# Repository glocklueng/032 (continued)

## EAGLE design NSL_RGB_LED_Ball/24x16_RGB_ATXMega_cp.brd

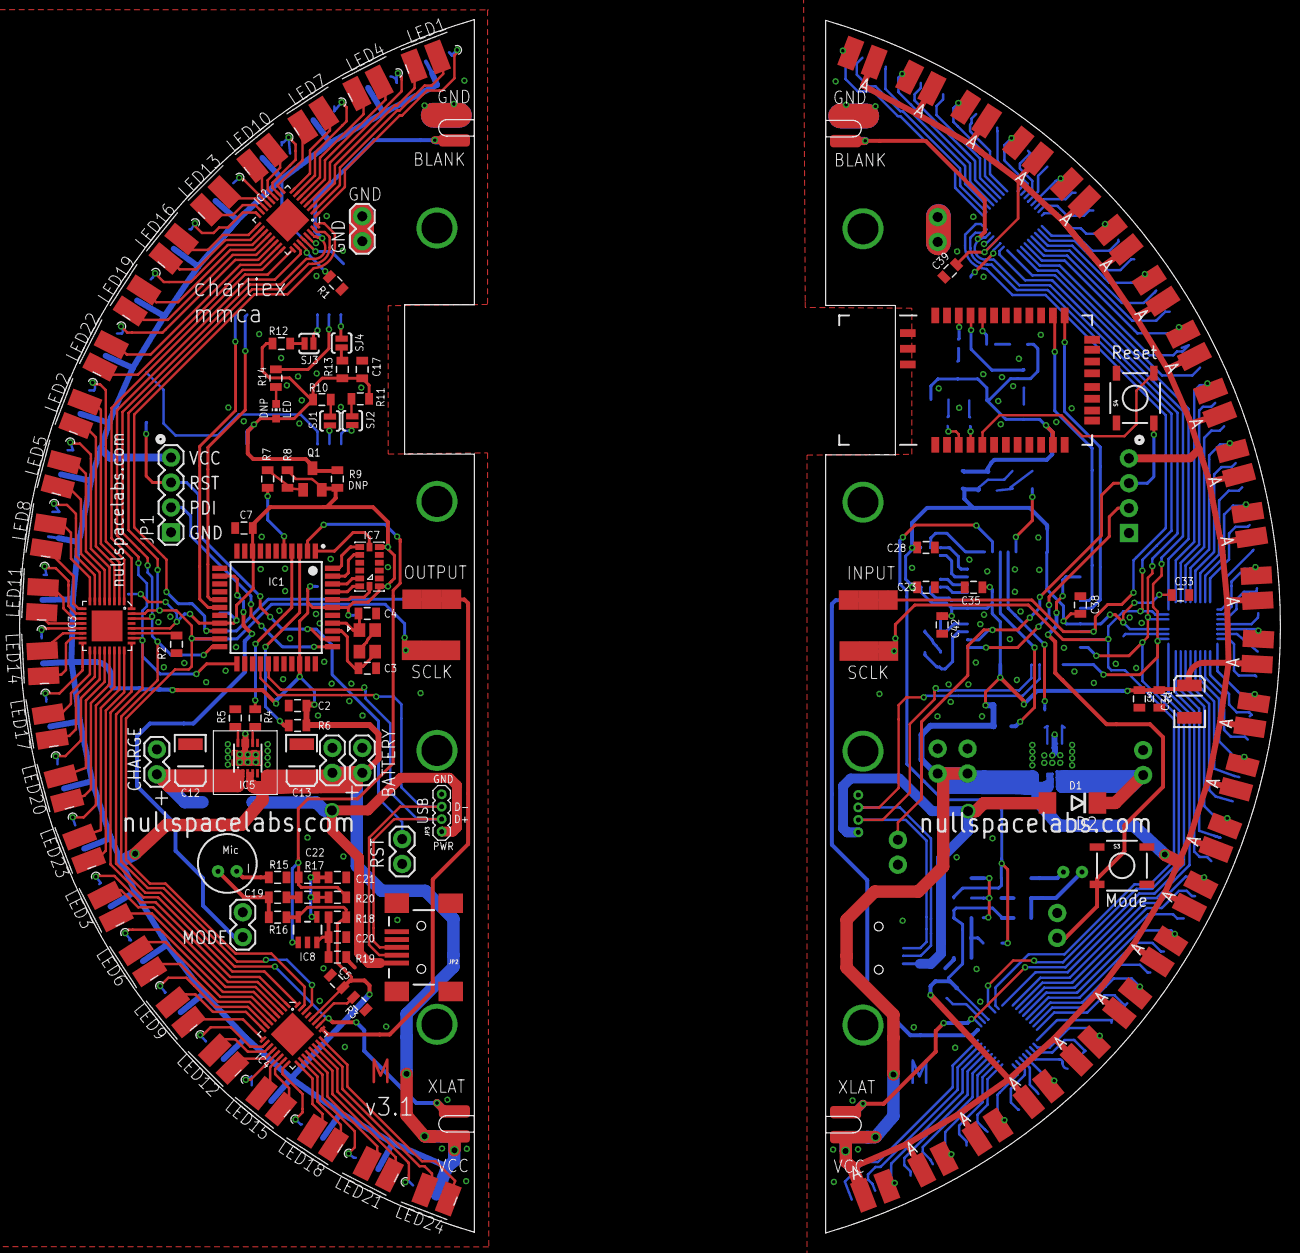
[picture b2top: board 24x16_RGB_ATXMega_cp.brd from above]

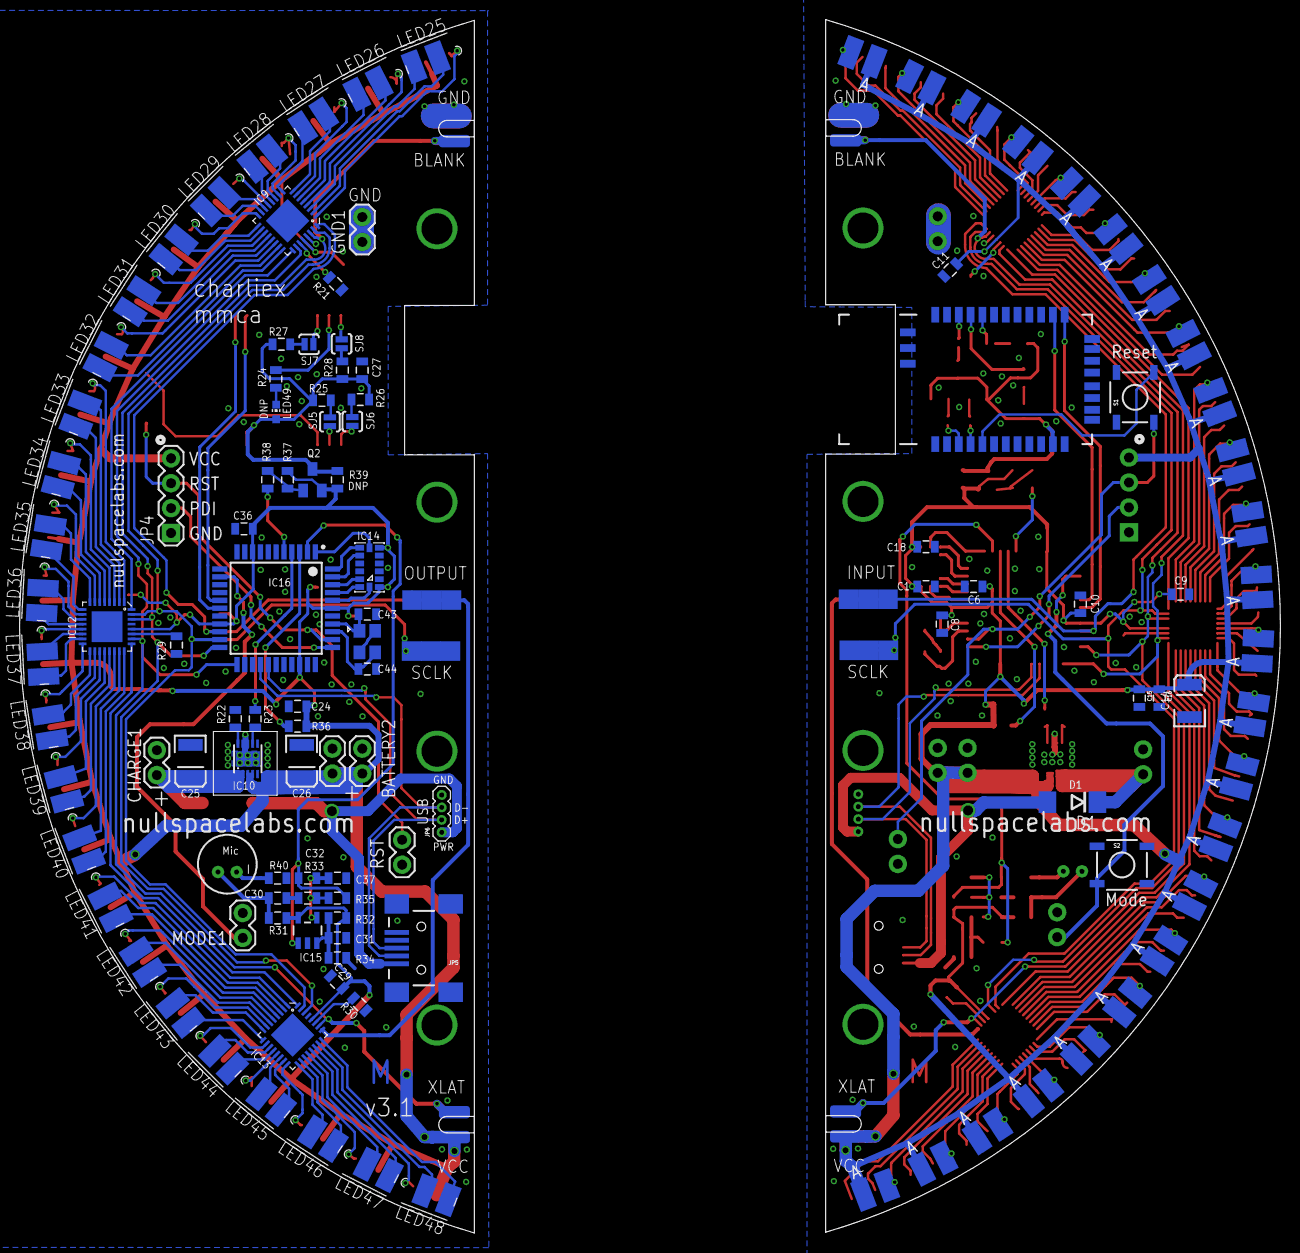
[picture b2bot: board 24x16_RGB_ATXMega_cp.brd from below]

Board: 2 copper layers, 128.6 x 123.8 mm, 216 parts (108 on the bottom side), 252 nets.

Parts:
BATTERY, BATTERY1, BATTERY2, BATTERY3: 1X02
C1, C2, C5, C6, C7, C9, C10, C11, C17, C21, C23, C24, C27, C29, C33, C35, C36, C37, C38, C39: .1uF; 0805
C3, C4, C43, C44: 10pF; 0805
C8, C18, C28, C42: 0.1uF; 0805
C12, C13, C25, C26: 4.7uF; EIA3528
C14, C34: 47uF; EIA3528
C15, C40: 10uF; 0805
C16, C20, C31, C41: 1uF; 0805
C19, C30: 4.7uF; 0805
C22, C32: 12pF; 0805
CHARGE, CHARGE1: 1X02
D1, D2: SSB44-E3/52T; DO214AA
GND, GND1: 1X02
IC1, IC16: NONOLITH_TQFP-44
IC2, IC3, IC4, IC9, IC12, IC13: TLC5947XLP; QFN32_XLP
IC5, IC10: MCP73123; DFN10_3X3
IC6, IC11: BLUETOOTH-RN41"; RN41
IC7, IC14: MMA7455L; LGA-14
IC8, IC15: OPA344; SOT23-5
JP1, JP4: 1X04
JP2, JP5: USBSMD; USB-MINIB
JP3, JP6: 1X04-1.27MM
LED, LED49: CHIP-LED0603
LED1, LED2, LED3, LED4, LED5, LED6, LED7, LED8, LED9, LED10, LED11, LED12, LED13, LED14, LED15, LED16, LED17, LED18, LED19, LED20, LED21, LED22, LED23, LED24, LED25, LED26, LED27, LED28, LED29, LED30, LED31, LED32, LED33, LED34, LED35, LED36, LED37, LED38, LED39, LED40, LED41, LED42, LED43, LED44, LED45, LED46, LED47, LED48: GM1WA55311A5MM_RGB_EDGE; LED5MM_RGB_EDGE
MIC1, MIC2: MIC6MM; MIC-6MM
MODE, MODE1: 1X02
Q1, Q2: BSH201; SOT23
R1, R2, R3, R21, R29, R30: 20K; 0805
R4, R5, R22, R23: 1K; 0805
R6, R36: 220K; 0805
R7, R8, R17, R18, R19, R32, R33, R34, R37, R38: 10k; 0805
R9, R39: 0ohm DNP; 0805
R10, R11, R12, R13, R25, R26, R27, R28: 1k; 0805
R14, R24: 220; 0805
R15, R40: 4.7k; 0805
R16, R31: 2.2k; 0805
R20, R35: 1M; 0805
RST, RST1: 1X02
S1, S2, S3, S4: TACTILE_SWITCH_SMD
SJ1, SJ2, SJ3, SJ4, SJ5, SJ6, SJ7, SJ8: SOLDERJUMPERNO; SJ_2S-NO
SLOT1, SLOT2, SLOT3, SLOT4: SLOT
TP1, TP2, TP3, TP4, TP5, TP6, TP7, TP8, TP9, TP10, TP11, TP12, TP13, TP14, TP15, TP16, TP17, TP18, TP19, TP20, TP21, TP22, TP23, TP24: TPTP20SQ; TP20SQ
X1, X2: NX3225GA XC1972CT-ND; NX3225GA

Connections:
!CS: IC1.1, IC7.7
!CS1: IC14.7, IC16.1
BATTSENSE: IC1.3, R6.2
BATTSENSE1: IC16.3, R36.2
BLANK: IC1.22, IC2.30, IC3.30, IC4.30, SLOT2.P$1, SLOT2.P$3
BLANK1: IC9.30, IC12.30, IC13.30, IC16.22, SLOT4.P$1, SLOT4.P$3
BT_PWR: IC1.5, R7.2
BT_PWR1: IC16.5, R38.2
BT_RST: IC6.5, S1.4
BT_RST1: IC11.5, S4.4
BUTTON: IC1.13, MODE.2, S2.3
BUTTON1: IC16.13, MODE1.2, S3.3
CHARGE: C12.A, CHARGE.2, D1.C, IC5.1, IC5.2
CHARGE1: C25.A, CHARGE1.2, D2.C, IC10.1, IC10.2
COL1: IC2.1, LED1.B
COL2: IC2.2, LED1.G
COL3: IC2.3, LED1.R
COL4: IC2.4, LED4.B
COL5: IC2.5, LED4.G
COL6: IC2.6, LED4.R
COL7: IC2.7, LED7.B
COL8: IC2.8, LED7.G
COL9: IC2.9, LED7.R
COL10: IC2.10, LED10.B
COL11: IC2.11, LED10.G
COL12: IC2.12, LED10.R
COL13: IC2.13, LED13.B
COL14: IC2.14, LED13.G
COL15: IC2.15, LED13.R
COL16: IC2.16, LED16.B
COL17: IC2.17, LED16.G
COL18: IC2.18, LED16.R
COL19: IC2.19, LED19.B
COL20: IC2.20, LED19.G
COL21: IC2.21, LED19.R
COL22: IC2.22, LED22.B
COL23: IC2.23, LED22.G
COL24: IC2.24, LED22.R
COL25: IC3.1, LED2.B
COL26: IC3.2, LED2.G
COL27: IC3.3, LED2.R
COL28: IC3.4, LED5.B
COL29: IC3.5, LED5.G
COL30: IC3.6, LED5.R
COL31: IC3.7, LED8.B
COL32: IC3.8, LED8.G
COL33: IC3.9, LED8.R
COL34: IC3.10, LED11.B
COL35: IC3.11, LED11.G
COL36: IC3.12, LED11.R
COL37: IC3.13, LED14.B
COL38: IC3.14, LED14.G
COL39: IC3.15, LED14.R
COL40: IC3.16, LED17.B
COL41: IC3.17, LED17.G
COL42: IC3.18, LED17.R
COL43: IC3.19, LED20.B
COL44: IC3.20, LED20.G
COL45: IC3.21, LED20.R
COL46: IC3.22, LED23.B
COL47: IC3.23, LED23.G
COL48: IC3.24, LED23.R
COL49: IC4.1, LED3.B
COL50: IC4.2, LED3.G
COL51: IC4.3, LED3.R
COL52: IC4.4, LED6.B
COL53: IC4.5, LED6.G
COL54: IC4.6, LED6.R
COL55: IC4.7, LED9.B
COL56: IC4.8, LED9.G
COL57: IC4.9, LED9.R
COL58: IC4.10, LED12.B
COL59: IC4.11, LED12.G
COL60: IC4.12, LED12.R
COL61: IC4.13, LED15.B
COL62: IC4.14, LED15.G
COL63: IC4.15, LED15.R
COL64: IC4.16, LED18.B
COL65: IC4.17, LED18.G
COL66: IC4.18, LED18.R
COL67: IC4.19, LED21.B
COL68: IC4.20, LED21.G
COL69: IC4.21, LED21.R
COL70: IC4.22, LED24.B
COL71: IC4.23, LED24.G
COL72: IC4.24, LED24.R
COL73: IC9.2, LED25.G
COL74: IC9.4, LED26.B
COL75: IC9.5, LED26.G
COL76: IC9.7, LED27.B
COL77: IC9.8, LED27.G
COL78: IC9.10, LED28.B
COL79: IC9.11, LED28.G
COL80: IC9.13, LED29.B
COL81: IC9.14, LED29.G
COL82: IC9.17, LED30.G
COL83: IC9.19, LED31.B
COL84: IC9.20, LED31.G
COL85: IC9.23, LED32.G
COL86: IC9.22, LED32.B
COL87: IC9.16, LED30.B
COL88: IC9.1, LED25.B
COL89: IC9.3, LED25.R
COL90: IC9.6, LED26.R
COL91: IC9.9, LED27.R
COL92: IC9.12, LED28.R
COL93: IC9.15, LED29.R
COL94: IC9.18, LED30.R
COL95: IC9.21, LED31.R
COL96: IC9.24, LED32.R
COL97: IC12.3, LED33.R
COL98: IC12.1, LED33.B
COL99: IC12.2, LED33.G
COL100: IC12.4, LED34.B
COL101: IC12.5, LED34.G
COL102: IC12.6, LED34.R
COL103: IC12.7, LED35.B
COL104: IC12.8, LED35.G
COL105: IC12.9, LED35.R
COL106: IC12.10, LED36.B
COL107: IC12.11, LED36.G
COL108: IC12.12, LED36.R
COL109: IC12.13, LED37.B
COL110: IC12.14, LED37.G
COL111: IC12.15, LED37.R
COL112: IC12.16, LED38.B
COL113: IC12.17, LED38.G
COL114: IC12.18, LED38.R
COL115: IC12.19, LED39.B
COL116: IC12.20, LED39.G
COL117: IC12.21, LED39.R
COL118: IC12.22, LED40.B
COL119: IC12.23, LED40.G
COL120: IC12.24, LED40.R
COL121: IC13.1, LED41.B
COL122: IC13.2, LED41.G
COL123: IC13.4, LED42.B
COL124: IC13.3, LED41.R
COL125: IC13.5, LED42.G
COL126: IC13.6, LED42.R
COL127: IC13.7, LED43.B
COL128: IC13.8, LED43.G
COL129: IC13.9, LED43.R
COL130: IC13.10, LED44.B
COL131: IC13.11, LED44.G
COL132: IC13.12, LED44.R
COL133: IC13.13, LED45.B
COL134: IC13.14, LED45.G
COL135: IC13.15, LED45.R
COL136: IC13.16, LED46.B
COL137: IC13.17, LED46.G
COL138: IC13.18, LED46.R
COL139: IC13.19, LED47.B
COL140: IC13.20, LED47.G
COL141: IC13.21, LED47.R
COL142: IC13.22, LED48.B
COL143: IC13.23, LED48.G
COL144: IC13.24, LED48.R
D+: IC1.27, JP2.D+, JP3.2
D+1: IC16.27, JP5.D+, JP6.2
D-: IC1.26, JP2.D-, JP3.3
D-1: IC16.26, JP5.D-, JP6.3
DAT: IC1.34, JP1.2
DAT1: IC16.34, JP4.2
DGND: X1.2, X1.4
DGND1: X2.2, X2.4
GND: BATTERY.1, BATTERY1.1, C1.2, C2.2, C3.1, C4.1, C5.2, C6.2, C7.2, C8.2, C9.2, C10.2, C11.2, C12.C, C13.C, C14.C, C15.2, C16.2, C17.2, C18.1, C20.1, C21.2, CHARGE.1, GND.1, GND.2, IC1.8, IC1.18, IC1.30, IC1.38, IC2.29, IC3.29, IC4.29, IC5.8, IC5.9, IC5.EXP, IC6.1, IC6.12, IC6.25, IC6.27, IC6.28, IC6.29, IC7.2, IC7.3, IC7.4, IC7.5, IC7.10, IC7.11, IC8.2, JP1.1, JP2.GND, JP3.4, MODE.1, R1.1, R2.1, R3.1, R5.1, R15.1, R19.2, RST.1, S1.1, S1.2, S2.1, S2.2, SLOT2.P$2, SLOT2.P$4
GND1: BATTERY2.1, BATTERY3.1, C23.2, C24.2, C25.C, C26.C, C27.2, C28.1, C29.2, C31.1, C33.2, C34.C, C35.2, C36.2, C37.2, C38.2, C39.2, C40.2, C41.2, C42.2, C43.1, C44.1, CHARGE1.1, GND1.1, GND1.2, IC9.29, IC10.8, IC10.9, IC10.EXP, IC11.1, IC11.12, IC11.25, IC11.27, IC11.28, IC11.29, IC12.29, IC13.29, IC14.2, IC14.3, IC14.4, IC14.5, IC14.10, IC14.11, IC15.2, IC16.8, IC16.18, IC16.30, IC16.38, JP4.1, JP5.GND, JP6.4, MODE1.1, R21.1, R22.1, R29.1, R30.1, R34.2, R40.1, RST1.1, S3.1, S3.2, S4.1, S4.2, SLOT4.P$2, SLOT4.P$4
HOLE: IC2.27, R1.2
HOLE1: IC9.27, R21.2
INT1: IC14.9, IC16.43
INT1/DRDY: IC1.44, IC7.8
INT1/DRDY1: IC14.8, IC16.44
INT2: IC1.43, IC7.9
MIC: C22.1, IC1.2, IC8.1, R20.2
MIC1: C32.1, IC15.1, IC16.2, R35.2
unnamed: IC5.7, R4.2
unnamed: IC3.27, R2.2
unnamed: IC2.25, IC3.32
unnamed: LED.C, R14.2
unnamed: R10.1, SJ1.2
unnamed: IC5.10, R5.2
unnamed: D1.A, JP2.VBUS, JP3.1
unnamed: IC10.10, R22.2
unnamed: IC4.27, R3.2
unnamed: C19.2, R17.2
unnamed: C19.1, MIC1.1, R16.1
unnamed: C20.2, IC8.3, R18.1, R19.1
unnamed: C21.1, C22.2, IC8.4, R17.1, R20.1
unnamed: Q1.1, R7.1, R8.1
unnamed: IC3.25, IC4.32
unnamed: MIC1.2, R15.2
unnamed: R12.1, SJ3.2
unnamed: IC10.7, R23.2
unnamed: R11.1, SJ2.2
unnamed: R13.1, SJ4.2
unnamed: LED49.C, R24.2
unnamed: R27.1, SJ7.2
unnamed: R25.1, SJ5.2
unnamed: R26.1, SJ6.2
unnamed: R28.1, SJ8.2
unnamed: IC12.27, R29.2
unnamed: IC9.25, IC12.32
unnamed: IC13.27, R30.2
unnamed: C3.2, IC1.36, X1.3
unnamed: C4.2, IC1.37, X1.1
unnamed: C30.2, R33.2
unnamed: C30.1, MIC2.1, R31.1
unnamed: C31.2, IC15.3, R32.1, R34.1
unnamed: C32.2, C37.1, IC15.4, R33.1, R35.1
unnamed: Q2.1, R37.1, R38.1
unnamed: IC12.25, IC13.32
unnamed: MIC2.2, R40.2
unnamed: C44.2, IC16.36, X2.3
unnamed: C43.2, IC16.37, X2.1
unnamed: D2.A, JP5.VBUS, JP6.1
PIO1: IC11.21, R24.1
PIO2: IC11.22, SJ8.1
PIO3: IC6.20, SJ3.1
PIO4: IC6.22, SJ4.1
PIO5: IC6.21, R14.1
PIO6: IC6.3, SJ2.1
PIO7: IC6.4, SJ1.1
PIO8: IC11.3, SJ6.1
PIO9: IC11.4, SJ5.1
PIO10: IC11.20, SJ7.1
RST: IC1.35, JP1.3, RST.2, S1.3
RST1: IC16.35, JP4.3, RST1.2, S4.3
RX: IC1.16, IC6.14
RX1: IC11.14, IC16.16
SCL/SPC: IC1.41, IC7.13
SCL/SPC1: IC14.13, IC16.41
SCLK: IC1.21, IC2.31, IC3.31, IC4.31, TP3.TP, TP4.TP, TP7.TP, TP8.TP, TP10.TP, TP12.TP
SCLK1: IC9.31, IC12.31, IC13.31, IC16.21, TP15.TP, TP16.TP, TP19.TP, TP20.TP, TP22.TP, TP24.TP
SDA/SDI/SDO: IC1.42, IC7.12
SDA/SDI/SDO1: IC14.12, IC16.42
SDO: IC1.40, IC7.14
SDO1: IC14.14, IC16.40
SIN: IC1.20, IC2.32, TP5.TP, TP6.TP, TP11.TP
SIN1: IC9.32, IC16.20, TP17.TP, TP18.TP, TP23.TP
SOUT: IC4.25, TP1.TP, TP2.TP, TP9.TP
SOUT1: IC13.25, TP13.TP, TP14.TP, TP21.TP
STAT: IC1.4, R4.1
STAT1: IC16.4, R23.1
TX: IC1.17, IC6.13
TX1: IC11.13, IC16.17
VCC: BATTERY.2, BATTERY1.2, C1.1, C2.1, C5.1, C6.1, C7.1, C8.1, C9.1, C10.1, C11.1, C13.A, C14.A, C15.1, C16.1, C18.2, IC1.9, IC1.19, IC1.31, IC1.39, IC2.28, IC3.28, IC4.28, IC5.3, IC5.4, IC7.1, IC7.6, IC8.5, JP1.4, LED1.A, LED2.A, LED3.A, LED4.A, LED5.A, LED6.A, LED7.A, LED8.A, LED9.A, LED10.A, LED11.A, LED12.A, LED13.A, LED14.A, LED15.A, LED16.A, LED17.A, LED18.A, LED19.A, LED20.A, LED21.A, LED22.A, LED23.A, LED24.A, Q1.2, R6.1, R8.2, R9.2, R16.2, R18.2, SLOT1.P$1, SLOT1.P$3
VCC1: BATTERY2.2, BATTERY3.2, C23.1, C24.1, C26.A, C28.2, C29.1, C33.1, C34.A, C35.1, C36.1, C38.1, C39.1, C40.1, C41.1, C42.1, IC9.28, IC10.3, IC10.4, IC12.28, IC13.28, IC14.1, IC14.6, IC15.5, IC16.9, IC16.19, IC16.31, IC16.39, JP4.4, LED25.A, LED26.A, LED27.A, LED28.A, LED29.A, LED30.A, LED31.A, LED32.A, LED33.A, LED34.A, LED35.A, LED36.A, LED37.A, LED38.A, LED39.A, LED40.A, LED41.A, LED42.A, LED43.A, LED44.A, LED45.A, LED46.A, LED47.A, LED48.A, Q2.2, R31.2, R32.2, R36.1, R37.2, R39.2, SLOT3.P$1, SLOT3.P$3
VDD: C17.1, IC6.11, LED.A, Q1.3, R9.1, R10.2, R11.2, R12.2, R13.2
VDD1: C27.1, IC11.11, LED49.A, Q2.3, R25.2, R26.2, R27.2, R28.2, R39.1
XLAT: IC1.23, IC2.26, IC3.26, IC4.26, SLOT1.P$2, SLOT1.P$4
XLAT1: IC9.26, IC12.26, IC13.26, IC16.23, SLOT3.P$2, SLOT3.P$4

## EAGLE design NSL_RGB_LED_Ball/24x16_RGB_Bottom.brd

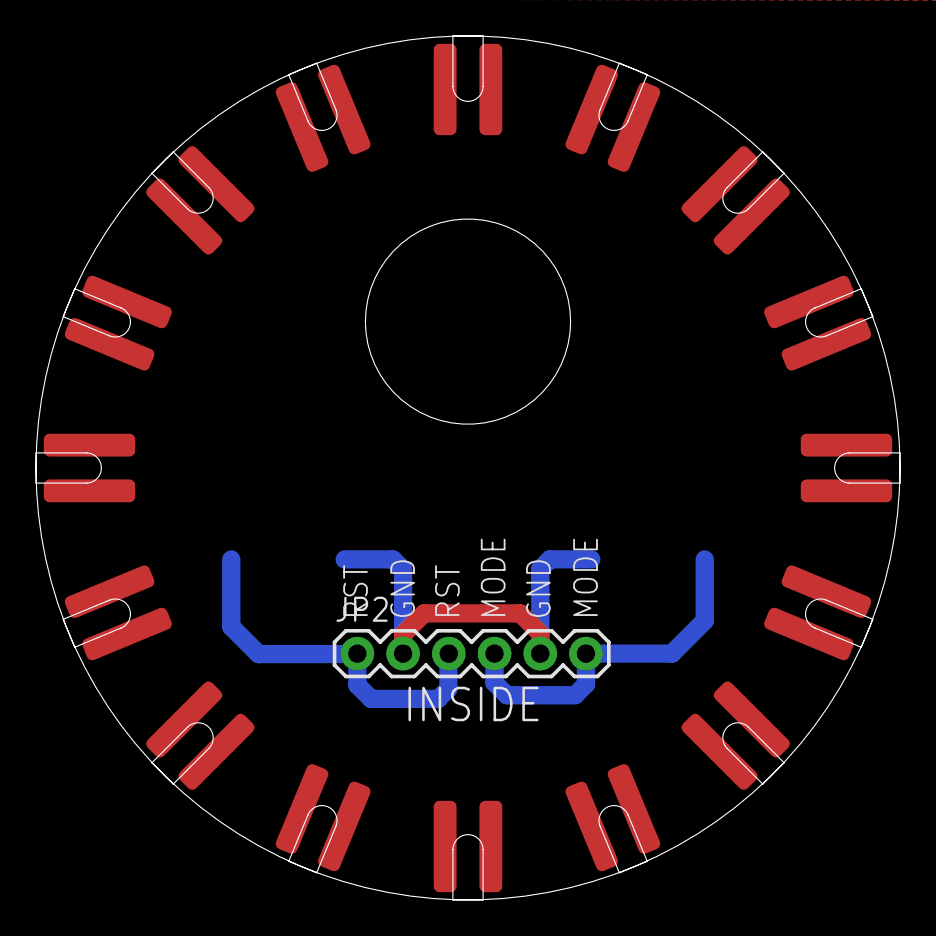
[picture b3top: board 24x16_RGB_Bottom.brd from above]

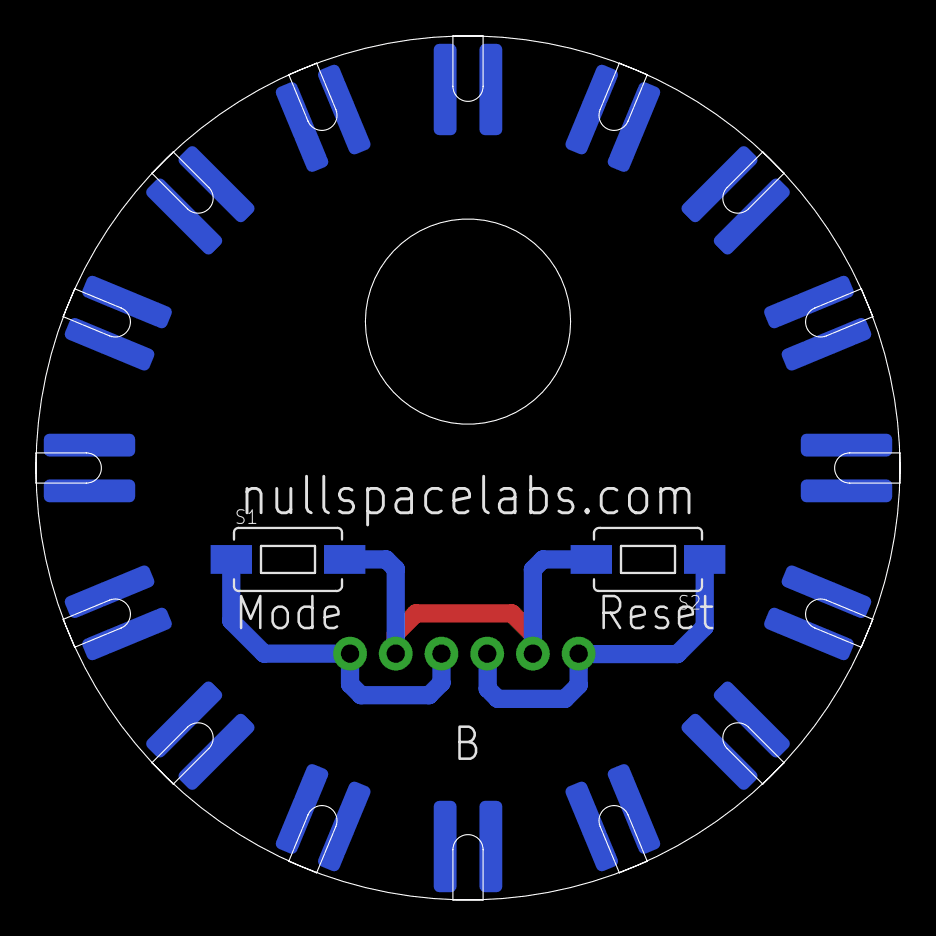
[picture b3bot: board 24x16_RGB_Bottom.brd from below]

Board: 2 copper layers, 48.0 x 48.0 mm, 20 parts (2 on the bottom side), 5 nets.

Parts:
JP2: 1X06
S1, S2: SPARKFUN-ELECTROMECHANICAL_SWITCH-MOMENTARY-2-SMD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; SPARKFUN-ELECTROMECHANICAL_TACTILE-SWITCH-1101NE
SLOT1, SLOT2, SLOT3, SLOT4, SLOT5, SLOT6, SLOT7, SLOT8, SLOT9, SLOT10, SLOT11, SLOT12, SLOT13, SLOT14, SLOT15, SLOT16: SLOT
U$1: DC_PWR; DC_2.1

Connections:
GND: JP2.2, JP2.5, S1.P$2, S2.P$2
MODE: JP2.4, JP2.6, S1.P$1
RST: JP2.1, JP2.3, S2.P$1
VCC: SLOT1.P$3, SLOT1.P$4, SLOT2.P$3, SLOT2.P$4, SLOT3.P$3, SLOT3.P$4, SLOT4.P$3, SLOT4.P$4, SLOT5.P$3, SLOT5.P$4, SLOT6.P$3, SLOT6.P$4, SLOT7.P$3, SLOT7.P$4, SLOT8.P$3, SLOT8.P$4, SLOT9.P$3, SLOT9.P$4, SLOT10.P$3, SLOT10.P$4, SLOT11.P$3, SLOT11.P$4, SLOT12.P$3, SLOT12.P$4, SLOT13.P$3, SLOT13.P$4, SLOT14.P$3, SLOT14.P$4, SLOT15.P$3, SLOT15.P$4, SLOT16.P$3, SLOT16.P$4
XLAT: SLOT1.P$1, SLOT1.P$2, SLOT2.P$1, SLOT2.P$2, SLOT3.P$1, SLOT3.P$2, SLOT4.P$1, SLOT4.P$2, SLOT5.P$1, SLOT5.P$2, SLOT6.P$1, SLOT6.P$2, SLOT7.P$1, SLOT7.P$2, SLOT8.P$1, SLOT8.P$2, SLOT9.P$1, SLOT9.P$2, SLOT10.P$1, SLOT10.P$2, SLOT11.P$1, SLOT11.P$2, SLOT12.P$1, SLOT12.P$2, SLOT13.P$1, SLOT13.P$2, SLOT14.P$1, SLOT14.P$2, SLOT15.P$1, SLOT15.P$2, SLOT16.P$1, SLOT16.P$2

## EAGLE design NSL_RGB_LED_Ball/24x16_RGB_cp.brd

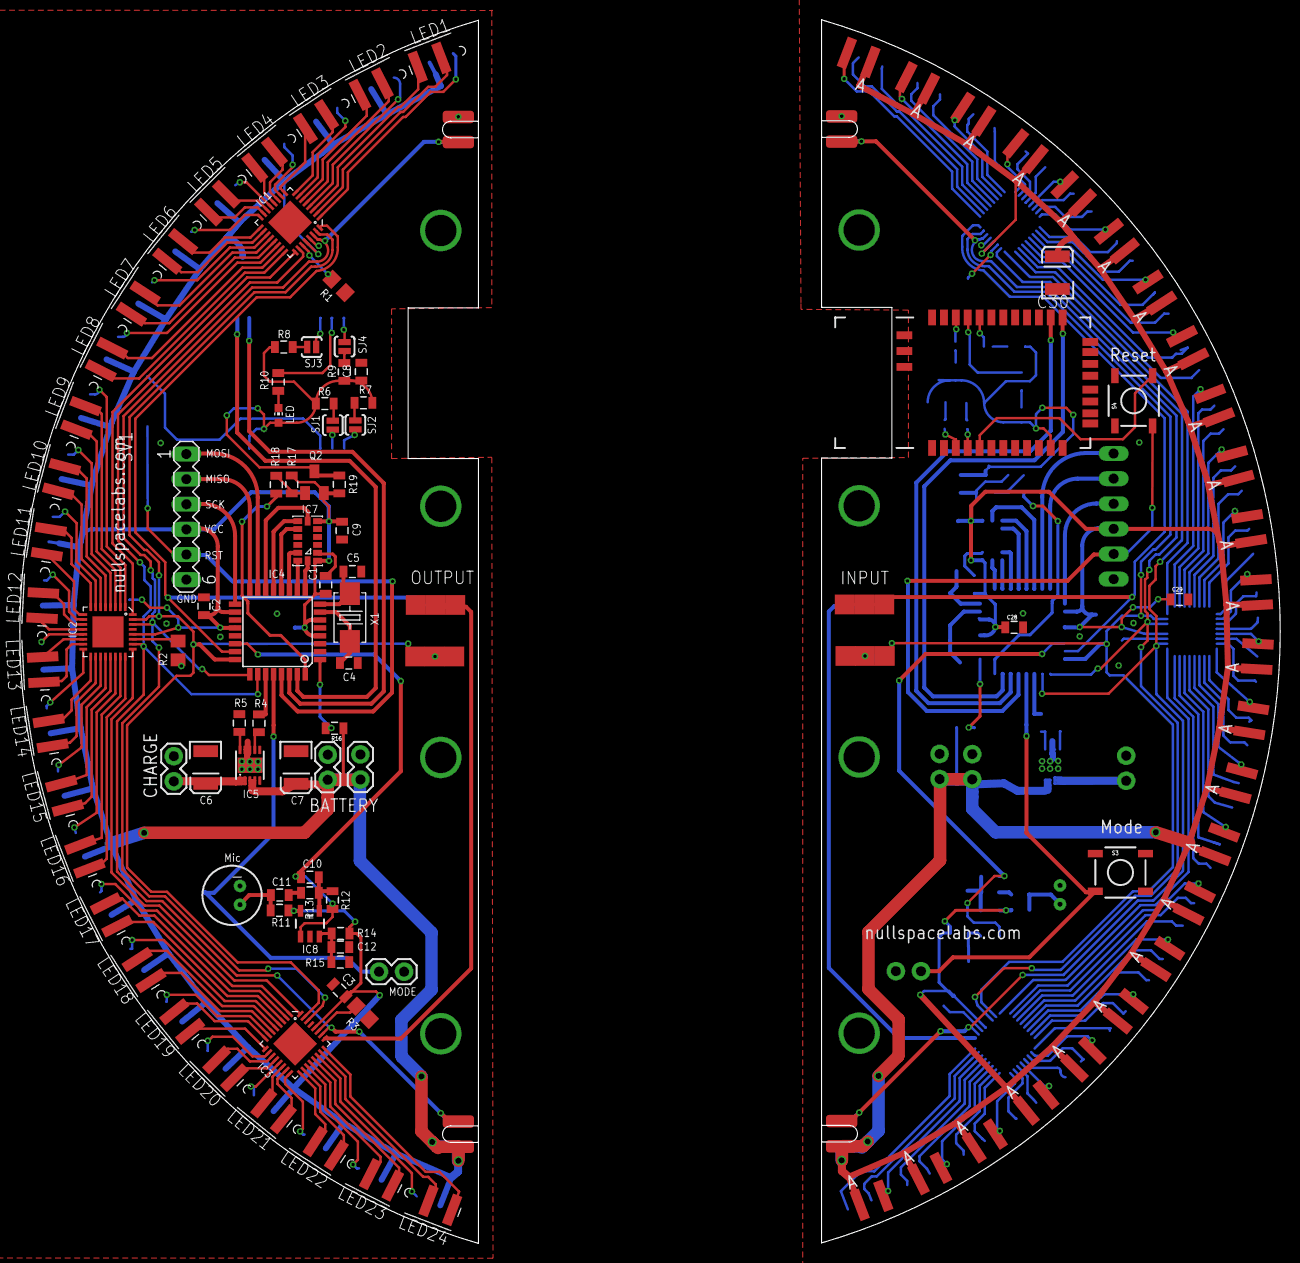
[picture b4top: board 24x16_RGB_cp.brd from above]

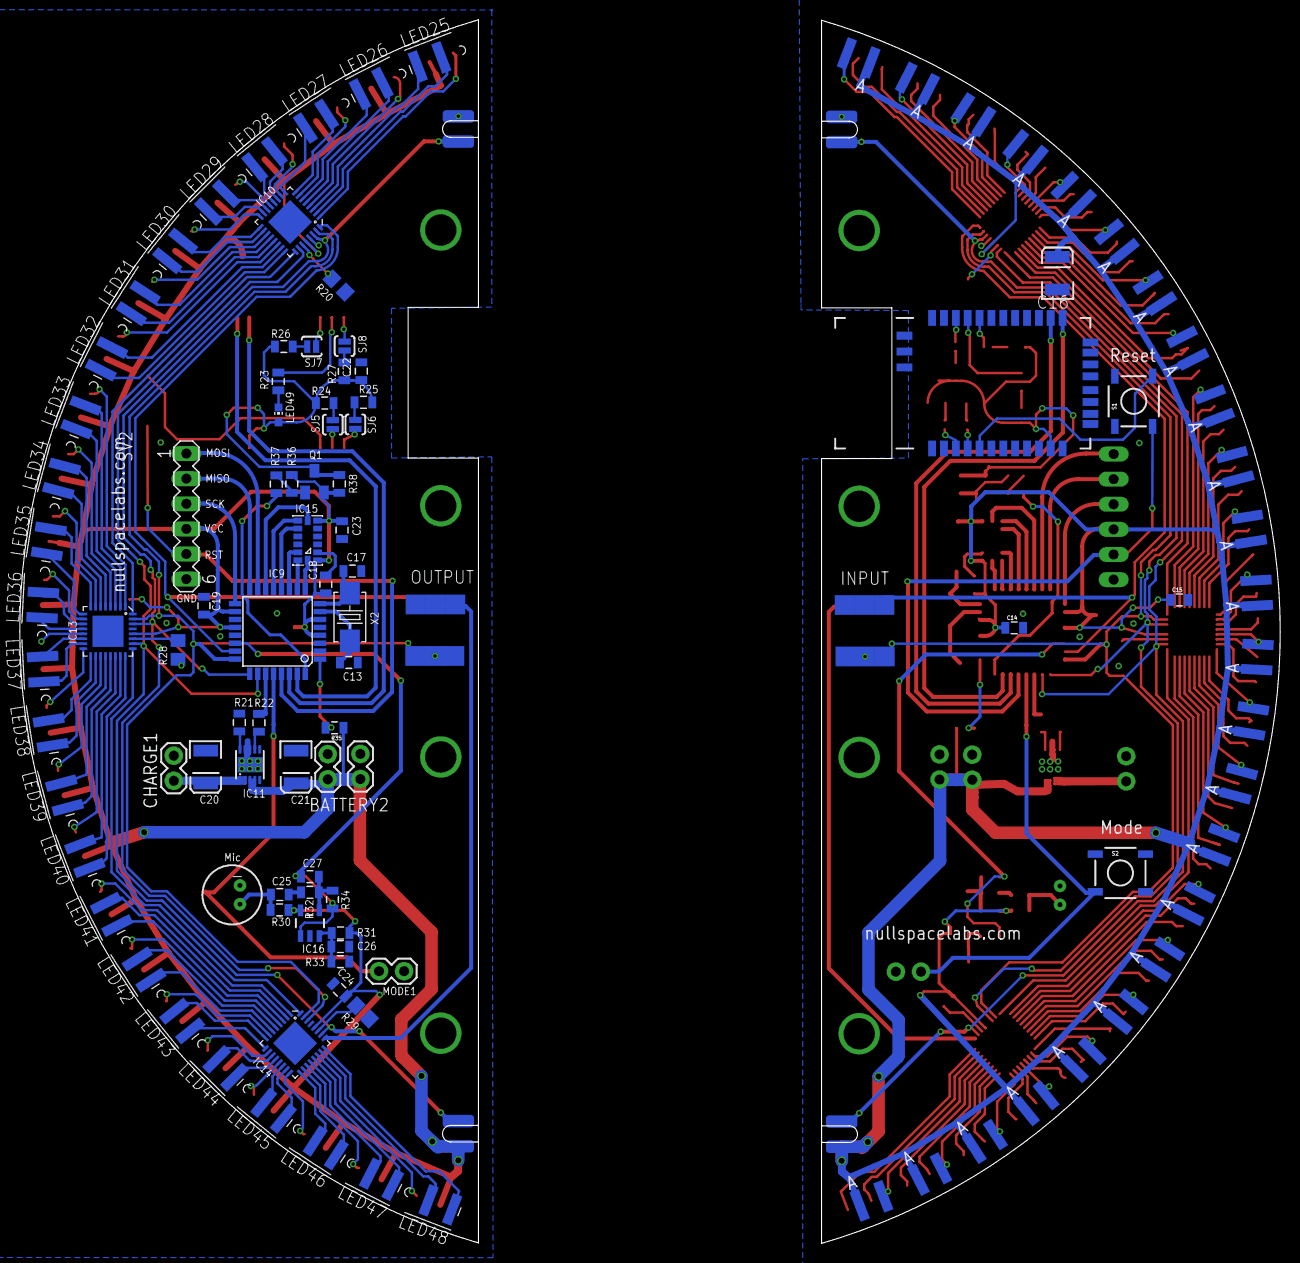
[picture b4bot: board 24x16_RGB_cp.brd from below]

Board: 2 copper layers, 127.5 x 123.7 mm, 190 parts (95 on the bottom side), 246 nets.

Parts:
BATTERY, BATTERY1, BATTERY2, BATTERY3: 1X02
C1, C2, C3, C8, C11, C14, C15, C18, C19, C22, C24, C25, C28, C29: .1uF; 0805
C4, C5, C13, C17: 18pF; 0805
C6, C7, C16, C20, C21, C30: 4.7uF; EIA3528
C9, C23: 0.1uF; 0805
C10, C27: 100pF; 0805
C12, C26: 1uF; 0805
CHARGE, CHARGE1: 1X02
IC1, IC2, IC3, IC10, IC13, IC14: TLC5947XLP; QFN32_XLP
IC4, IC9: MEGA8-AI; TQFP32-08
IC5, IC11: MCP73123; DFN10_3X3
IC6, IC12: BLUETOOTH-RN41"; RN41
IC7, IC15: MMA7455L; LGA-14
IC8, IC16: OPA344; SOT23-5
LED, LED49: CHIP-LED0603
LED1, LED2, LED3, LED4, LED5, LED6, LED7, LED8, LED9, LED10, LED11, LED12, LED13, LED14, LED15, LED16, LED17, LED18, LED19, LED20, LED21, LED22, LED23, LED24, LED25, LED26, LED27, LED28, LED29, LED30, LED31, LED32, LED33, LED34, LED35, LED36, LED37, LED38, LED39, LED40, LED41, LED42, LED43, LED44, LED45, LED46, LED47, LED48: GM1WA55311A5MM_RGB_EDGE; LED5MM_RGB_EDGE
MIC1, MIC2: MIC6MM; MIC-6MM
MODE, MODE1: 1X02
Q1, Q2: BSH201; SOT23
R1, R2, R3, R20, R28, R29: 20K; R0805
R4, R22: 1K; 0805
R5, R21: 1.5K; 0805
R6, R7, R8, R9, R13, R24, R25, R26, R27, R32: 1k; 0805
R10, R23: 220; 0805
R11, R30: 2.2k; 0805
R12, R34: 100K; 0805
R14, R15, R17, R18, R31, R33, R36, R37: 10k; 0805
R16, R35: 220K; 0805
R19, R38: 0ohm DNP; 0805
S1, S2, S3, S4: TACTILE_SWITCH_SMD
SJ1, SJ2, SJ3, SJ4, SJ5, SJ6, SJ7, SJ8: SOLDERJUMPERNO; SJ_2S-NO
SLOT1, SLOT2, SLOT3, SLOT4: SLOT
SV1, SV2: MA06-1
TP1, TP2, TP3, TP4, TP5, TP6, TP7, TP8, TP9, TP10, TP11, TP12, TP13, TP14, TP15, TP16, TP17, TP18, TP19, TP20, TP21, TP22, TP23, TP24: TPTP20SQ; TP20SQ
X1, X2: 16Mhz; 5032

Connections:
!CS: IC4.14, IC7.7
!CS1: IC9.14, IC15.7
BATTSENSE: IC4.1, R16.2
BATTSENSE1: IC9.1, R35.2
BLANK: IC1.30, IC2.30, IC3.30, IC4.25, SLOT2.P$1, SLOT2.P$3
BLANK1: IC9.25, IC10.30, IC13.30, IC14.30, SLOT4.P$1, SLOT4.P$3
BT_PWR: IC4.32, R18.2
BT_PWR1: IC9.32, R37.2
BT_RST: IC6.5, S1.4
BT_RST1: IC12.5, S4.4
BUTTON: IC4.28, MODE.2, S2.3
BUTTON1: IC9.28, MODE1.2, S3.3
CHARGE: C6.A, CHARGE.2, IC5.1, IC5.2
CHARGE1: C20.A, CHARGE1.2, IC11.1, IC11.2
COL1: IC1.1, LED1.B
COL2: IC1.2, LED1.G
COL3: IC1.3, LED1.R
COL4: IC1.4, LED2.B
COL5: IC1.5, LED2.G
COL6: IC1.6, LED2.R
COL7: IC1.7, LED3.B
COL8: IC1.8, LED3.G
COL9: IC1.9, LED3.R
COL10: IC1.10, LED4.B
COL11: IC1.11, LED4.G
COL12: IC1.12, LED4.R
COL13: IC1.13, LED5.B
COL14: IC1.14, LED5.G
COL15: IC1.15, LED5.R
COL16: IC1.16, LED6.B
COL17: IC1.17, LED6.G
COL18: IC1.18, LED6.R
COL19: IC1.19, LED7.B
COL20: IC1.20, LED7.G
COL21: IC1.21, LED7.R
COL22: IC1.22, LED8.B
COL23: IC1.23, LED8.G
COL24: IC1.24, LED8.R
COL25: IC2.1, LED9.B
COL26: IC2.2, LED9.G
COL27: IC2.3, LED9.R
COL28: IC2.4, LED10.B
COL29: IC2.5, LED10.G
COL30: IC2.6, LED10.R
COL31: IC2.7, LED11.B
COL32: IC2.8, LED11.G
COL33: IC2.9, LED11.R
COL34: IC2.10, LED12.B
COL35: IC2.11, LED12.G
COL36: IC2.12, LED12.R
COL37: IC2.13, LED13.B
COL38: IC2.14, LED13.G
COL39: IC2.15, LED13.R
COL40: IC2.16, LED14.B
COL41: IC2.17, LED14.G
COL42: IC2.18, LED14.R
COL43: IC2.19, LED15.B
COL44: IC2.20, LED15.G
COL45: IC2.21, LED15.R
COL46: IC2.22, LED16.B
COL47: IC2.23, LED16.G
COL48: IC2.24, LED16.R
COL49: IC3.1, LED17.B
COL50: IC3.2, LED17.G
COL51: IC3.3, LED17.R
COL52: IC3.4, LED18.B
COL53: IC3.5, LED18.G
COL54: IC3.6, LED18.R
COL55: IC3.7, LED19.B
COL56: IC3.8, LED19.G
COL57: IC3.9, LED19.R
COL58: IC3.10, LED20.B
COL59: IC3.11, LED20.G
COL60: IC3.12, LED20.R
COL61: IC3.13, LED21.B
COL62: IC3.14, LED21.G
COL63: IC3.15, LED21.R
COL64: IC3.16, LED22.B
COL65: IC3.17, LED22.G
COL66: IC3.18, LED22.R
COL67: IC3.19, LED23.B
COL68: IC3.20, LED23.G
COL69: IC3.21, LED23.R
COL70: IC3.22, LED24.B
COL71: IC3.23, LED24.G
COL72: IC3.24, LED24.R
COL73: IC10.2, LED25.G
COL74: IC10.4, LED26.B
COL75: IC10.5, LED26.G
COL76: IC10.7, LED27.B
COL77: IC10.8, LED27.G
COL78: IC10.10, LED28.B
COL79: IC10.11, LED28.G
COL80: IC10.13, LED29.B
COL81: IC10.14, LED29.G
COL82: IC10.17, LED30.G
COL83: IC10.19, LED31.B
COL84: IC10.20, LED31.G
COL85: IC10.23, LED32.G
COL86: IC10.22, LED32.B
COL87: IC10.16, LED30.B
COL88: IC10.1, LED25.B
COL89: IC10.3, LED25.R
COL90: IC10.6, LED26.R
COL91: IC10.9, LED27.R
COL92: IC10.12, LED28.R
COL93: IC10.15, LED29.R
COL94: IC10.18, LED30.R
COL95: IC10.21, LED31.R
COL96: IC10.24, LED32.R
COL97: IC13.3, LED33.R
COL98: IC13.1, LED33.B
COL99: IC13.2, LED33.G
COL100: IC13.4, LED34.B
COL101: IC13.5, LED34.G
COL102: IC13.6, LED34.R
COL103: IC13.7, LED35.B
COL104: IC13.8, LED35.G
COL105: IC13.9, LED35.R
COL106: IC13.10, LED36.B
COL107: IC13.11, LED36.G
COL108: IC13.12, LED36.R
COL109: IC13.13, LED37.B
COL110: IC13.14, LED37.G
COL111: IC13.15, LED37.R
COL112: IC13.16, LED38.B
COL113: IC13.17, LED38.G
COL114: IC13.18, LED38.R
COL115: IC13.19, LED39.B
COL116: IC13.20, LED39.G
COL117: IC13.21, LED39.R
COL118: IC13.22, LED40.B
COL119: IC13.23, LED40.G
COL120: IC13.24, LED40.R
COL121: IC14.1, LED41.B
COL122: IC14.2, LED41.G
COL123: IC14.4, LED42.B
COL124: IC14.3, LED41.R
COL125: IC14.5, LED42.G
COL126: IC14.6, LED42.R
COL127: IC14.7, LED43.B
COL128: IC14.8, LED43.G
COL129: IC14.9, LED43.R
COL130: IC14.10, LED44.B
COL131: IC14.11, LED44.G
COL132: IC14.12, LED44.R
COL133: IC14.13, LED45.B
COL134: IC14.14, LED45.G
COL135: IC14.15, LED45.R
COL136: IC14.16, LED46.B
COL137: IC14.17, LED46.G
COL138: IC14.18, LED46.R
COL139: IC14.19, LED47.B
COL140: IC14.20, LED47.G
COL141: IC14.21, LED47.R
COL142: IC14.22, LED48.B
COL143: IC14.23, LED48.G
COL144: IC14.24, LED48.R
GND: BATTERY.1, BATTERY1.1, C1.2, C2.2, C3.2, C4.2, C5.2, C6.C, C7.C, C8.2, C9.1, C12.1, C14.2, C15.2, C16.C, CHARGE.1, IC1.29, IC2.29, IC3.29, IC4.3, IC4.5, IC4.21, IC5.8, IC5.9, IC5.EXP, IC6.1, IC6.12, IC6.25, IC6.27, IC6.28, IC6.29, IC7.2, IC7.3, IC7.4, IC7.5, IC7.10, IC7.11, IC8.2, MIC1.2, MODE.1, R1.1, R2.1, R3.1, R5.1, R15.2, S1.1, S1.2, S2.1, S2.2, SLOT2.P$2, SLOT2.P$4, SV1.6
GND1: BATTERY2.1, BATTERY3.1, C13.2, C17.2, C18.2, C19.2, C20.C, C21.C, C22.2, C23.1, C24.2, C26.1, C28.2, C29.2, C30.C, CHARGE1.1, IC9.3, IC9.5, IC9.21, IC10.29, IC11.8, IC11.9, IC11.EXP, IC12.1, IC12.12, IC12.25, IC12.27, IC12.28, IC12.29, IC13.29, IC14.29, IC15.2, IC15.3, IC15.4, IC15.5, IC15.10, IC15.11, IC16.2, MIC2.2, MODE1.1, R20.1, R21.1, R28.1, R29.1, R33.2, S3.1, S3.2, S4.1, S4.2, SLOT4.P$2, SLOT4.P$4, SV2.6
HOLE: IC1.27, R1.2
HOLE1: IC10.27, R20.2
INT1: IC9.12, IC15.9
INT1/DRDY: IC4.13, IC7.8
INT1/DRDY1: IC9.13, IC15.8
INT2: IC4.12, IC7.9
MIC: C10.1, IC4.22, IC8.1, R12.2
MIC1: C27.1, IC9.22, IC16.1, R34.2
MISO: IC4.16, SV1.2
MISO1: IC9.16, SV2.2
MOSI: IC4.15, SV1.1
MOSI1: IC9.15, SV2.1
unnamed: IC5.7, R4.2
unnamed: IC2.27, R2.2
unnamed: IC1.25, IC2.32
unnamed: LED.C, R10.2
unnamed: R6.1, SJ1.2
unnamed: IC5.10, R5.2
unnamed: C4.1, IC4.7, X1.2
unnamed: C5.1, IC4.8, X1.1
unnamed: IC3.27, R3.2
unnamed: C11.2, R13.2
unnamed: C11.1, MIC1.1, R11.1
unnamed: C12.2, IC8.3, R14.1, R15.1
unnamed: C10.2, IC8.4, R12.1, R13.1
unnamed: Q2.1, R17.1, R18.1
unnamed: IC2.25, IC3.32
unnamed: IC11.10, R21.2
unnamed: R8.1, SJ3.2
unnamed: IC11.7, R22.2
unnamed: R7.1, SJ2.2
unnamed: R9.1, SJ4.2
unnamed: LED49.C, R23.2
unnamed: R26.1, SJ7.2
unnamed: R24.1, SJ5.2
unnamed: R25.1, SJ6.2
unnamed: R27.1, SJ8.2
unnamed: IC13.27, R28.2
unnamed: IC10.25, IC13.32
unnamed: IC14.27, R29.2
unnamed: C25.2, R32.2
unnamed: C25.1, MIC2.1, R30.1
unnamed: C26.2, IC16.3, R31.1, R33.1
unnamed: C27.2, IC16.4, R32.1, R34.1
unnamed: Q1.1, R36.1, R37.1
unnamed: C13.1, IC9.7, X2.2
unnamed: C17.1, IC9.8, X2.1
unnamed: IC13.25, IC14.32
PIO1: IC12.21, R23.1
PIO2: IC12.22, SJ8.1
PIO3: IC6.20, SJ3.1
PIO4: IC6.22, SJ4.1
PIO5: IC6.21, R10.1
PIO6: IC6.3, SJ2.1
PIO7: IC6.4, SJ1.1
PIO8: IC12.3, SJ6.1
PIO9: IC12.4, SJ5.1
PIO10: IC12.20, SJ7.1
RST: IC4.29, S1.3, SV1.5
RST1: IC9.29, S4.3, SV2.5
RX: IC4.30, IC6.14
RX1: IC9.30, IC12.14
SCK: IC4.17, SV1.3
SCK1: IC9.17, SV2.3
SCL/SPC: IC4.10, IC7.13
SCL/SPC1: IC9.10, IC15.13
SCLK: IC1.31, IC2.31, IC3.31, IC4.24, TP3.TP, TP4.TP, TP7.TP, TP8.TP, TP10.TP, TP12.TP
SCLK1: IC9.24, IC10.31, IC13.31, IC14.31, TP15.TP, TP16.TP, TP19.TP, TP20.TP, TP22.TP, TP24.TP
SDA/SDI/SDO: IC4.11, IC7.12
SDA/SDI/SDO1: IC9.11, IC15.12
SDO: IC4.9, IC7.14
SDO1: IC9.9, IC15.14
SIN: IC1.32, IC4.23, TP5.TP, TP6.TP, TP11.TP
SIN1: IC9.23, IC10.32, TP17.TP, TP18.TP, TP23.TP
SOUT: IC3.25, TP1.TP, TP2.TP, TP9.TP
SOUT1: IC14.25, TP13.TP, TP14.TP, TP21.TP
STAT: IC4.27, R4.1
STAT1: IC9.27, R22.1
TX: IC4.31, IC6.13
TX1: IC9.31, IC12.13
VCC: BATTERY.2, BATTERY1.2, C1.1, C2.1, C3.1, C7.A, C9.2, C14.1, C15.1, C16.A, IC1.28, IC2.28, IC3.28, IC4.4, IC4.6, IC4.18, IC4.20, IC5.3, IC5.4, IC7.1, IC7.6, IC8.5, LED1.A, LED2.A, LED3.A, LED4.A, LED5.A, LED6.A, LED7.A, LED8.A, LED9.A, LED10.A, LED11.A, LED12.A, LED13.A, LED14.A, LED15.A, LED16.A, LED17.A, LED18.A, LED19.A, LED20.A, LED21.A, LED22.A, LED23.A, LED24.A, Q2.2, R11.2, R14.2, R16.1, R17.2, R19.2, SLOT1.P$1, SLOT1.P$3, SV1.4
VCC1: BATTERY2.2, BATTERY3.2, C18.1, C19.1, C21.A, C23.2, C24.1, C28.1, C29.1, C30.A, IC9.4, IC9.6, IC9.18, IC9.20, IC10.28, IC11.3, IC11.4, IC13.28, IC14.28, IC15.1, IC15.6, IC16.5, LED25.A, LED26.A, LED27.A, LED28.A, LED29.A, LED30.A, LED31.A, LED32.A, LED33.A, LED34.A, LED35.A, LED36.A, LED37.A, LED38.A, LED39.A, LED40.A, LED41.A, LED42.A, LED43.A, LED44.A, LED45.A, LED46.A, LED47.A, LED48.A, Q1.2, R30.2, R31.2, R35.1, R36.2, R38.2, SLOT3.P$1, SLOT3.P$3, SV2.4
VDD: C8.1, IC6.11, LED.A, Q2.3, R6.2, R7.2, R8.2, R9.2, R19.1
VDD1: C22.1, IC12.11, LED49.A, Q1.3, R24.2, R25.2, R26.2, R27.2, R38.1
XLAT: IC1.26, IC2.26, IC3.26, IC4.26, SLOT1.P$2, SLOT1.P$4
XLAT1: IC9.26, IC10.26, IC13.26, IC14.26, SLOT3.P$2, SLOT3.P$4

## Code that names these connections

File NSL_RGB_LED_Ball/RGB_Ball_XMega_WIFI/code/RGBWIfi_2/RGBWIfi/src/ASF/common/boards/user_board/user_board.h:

/**
 * \file
 *
 * \brief User board definition template
 *
 */

 /* This file is intended to contain definitions and configuration details for
 * features and devices that are available on the board, e.g., frequency and
 * startup time for an external crystal, external memory devices, LED and USART
 * pins.
 */

#ifndef USER_BOARD_H
#define USER_BOARD_H
#include <avr/io.h>
#include <util/delay.h>

#include <conf_board.h>

#ifndef NULL
#	define NULL ( 0) 
#endif

#define debug_str 
//__PROLOG 
#define debug_var(x,y)
#define debug_nl()
//	__PROLOG("\n")
#define debug_int_hex_16bit(x)
#define debug_int(x)
#define debug_putc(x)	
//circular_buffer_put(x)
#define debug_int_hex(x)

typedef unsigned char uint8_t;
typedef unsigned long uint32_t;
typedef signed char int8_t;
typedef long  int32_t;

#include "cc3000_general.h"

void timer(void );

#define NUM_TLC5947 ( 3 )

#define bit_set(reg, x) reg |= 1 << x
#define bit_clr(reg, x) reg &= ~(1 << x)

#define DATPIN		( PIN0_bp )    //    SIN
#define CLKPIN		( PIN1_bp )		//    SCLK
#define BLANKPIN	( PIN2_bp )		// BLANK
#define LATPIN		( PIN3_bp )		// XLAT
#define PORT_OUT	PORTD.OUT

// CC3000 WLAN IRQ pin

/*
PORTC.IN
	01234567
	11100011
PORTC.OUT
	01234567
	11000000
PORTC.DIR
	01234567
	11001101
PORTC.PIN6CTRL
	01234567
	00100000
PORTC.INTCTRL
	01234567
	10000000
PORTC.INT0MASK
	01234567
	00100000
PORTC.INT1MASK
	01234567
	00000000
*/

#define VIO				(PIN0_bp )
#define VIO_bm			(PIN0_bm )
#define VIO_bp			(PIN0_bp )

#define VBAT_SW_EN		(PIN1_bp )
#define VBAT_SW_EN_bm	(PIN1_bm )
#define VBAT_SW_EN_bp	(PIN1_bp )

#define WLAN_SPI_IRQ_bm	(PIN2_bm)	// SPI_IRQ (input)
#define WLAN_SPI_IRQ_bp	(PIN2_bp)	// SPI_IRQ (input)
#define WLAN_SS			(PIN4_bp)	// SPI_CS(output)
#define WLAN_SS_bm		(PIN4_bm)	// SPI_CS (output)
#define WLAN_MISO		(PIN6_bp)	// SPI_DOUT (input)
#define WLAN_MISO_bm	(PIN6_bm)	// SPI_DOUT (input)
#define WLAN_MOSI		(PIN5_bp)	// SPI_DIN(output)
#define WLAN_MOSI_bm	(PIN5_bm)	// SPI_DIN(output)
#define WLAN_SCK		(PIN7_bp)	// SPI_CLK(output)
#define WLAN_SCK_bm		(PIN7_bm)	// SPI_CLK(output)


#define SPI_SS_bm             WLAN_SS_bm		/*!< \brief Bit mask for the SS pin. */
#define SPI_MOSI_bm           WLAN_MOSI_bm		/*!< \brief Bit mask for the MOSI pin. */
#define SPI_MISO_bm           WLAN_MISO_bm		/*!< \brief Bit mask for the MISO pin. */
#define SPI_SCK_bm            WLAN_SCK_bm	/*!< \brief Bit mask for the SCK pin. */
#define SPI_IRQ_bm			  WLAN_SPI_IRQ_bm	/*!< \brief Bit mask for the SPI_IRQ pin/PC2 */


#define cc3000_spi_port	1

#define cc3000_cs_port	PORTC
#define cc3000_cs_pin	PIN4_bm

#define cc3000_int_port PORTC
#define cc3000_int_pin	PIN2_bm

#define cc3000_en_port PORTC
#define cc3000_en_pin  PIN1_bm

#define		set_pin(port,pin) { port.OUTSET=pin;} 
#define		make_output(port,pin)  { port.DIRSET = pin;}
#define		make_input(port,pin) { port.DIRCLR = pin;} 
#define		clear_pin(port,pin) { port.OUTCLR = pin;} 
#define		test_pin(port,pin)  (port.IN & pin)
	
#define clear_bit(port,pin)	{port.OUTCLR = pin;}
#define set_bit(port,pin)	{port.OUTSET = pin;}

// External oscillator settings.

// Uncomment and set correct values if external oscillator is used.

// External oscillator frequency
//#define BOARD_XOSC_HZ          8000000

// External oscillator type.
//!< External clock signal
//#define BOARD_XOSC_TYPE        XOSC_TYPE_EXTERNAL
//!< 32.768 kHz resonator on TOSC
//#define BOARD_XOSC_TYPE        XOSC_TYPE_32KHZ
//!< 0.4 to 16 MHz resonator on XTALS
//#define BOARD_XOSC_TYPE        XOSC_TYPE_XTAL

// External oscillator startup time
//#define BOARD_XOSC_STARTUP_US  500000
void Clear ( unsigned short val );

// TLC
void WriteLEDArray ( unsigned int count );
void LEDscan ( int red, float degreeoffset,unsigned int count );
void LED_Init ( void );
void LEDscan2Add ( int red, float degreeoffset,unsigned int count );
void WriteArrayOffset ( unsigned int count, unsigned int offset );
void SetPoint ( unsigned short x, unsigned short y,unsigned short val );

void WriteRGBArray ( void );
void RGBscan ( int red, int green, int blue, float degreeoffset );
void SetRGB ( unsigned short red, unsigned short green , unsigned short blue );


void dump_register(const unsigned char *str, register8_t port );

int circular_buffer_put ( unsigned char c );
int circular_buffer_puts ( char *str );
int circular_buffer_get ( unsigned char * const pc );
void circular_buffer_init(void);
int circular_empty(void);

int init_spi(void);

#ifndef __PROLOG
#define __PROLOG(X)		circular_buffer_puts(X)
#endif
#endif // USER_BOARD_H
